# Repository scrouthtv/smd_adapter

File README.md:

# Generic Adapters for SMD to THT
All SMD adapters are for 2.54mm header

## SOIC-16 -- small version

## SOIC-18 -- wide version

## SC-70-6

## SON10
Mostly used by european companies as the step is 1mm (I guess).

# Plugs
## MQ172 3-pin

No warranty for anything in this repo.

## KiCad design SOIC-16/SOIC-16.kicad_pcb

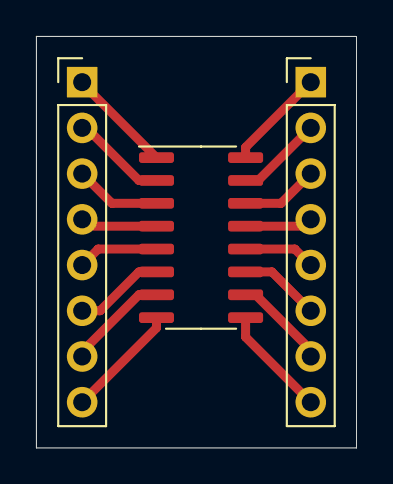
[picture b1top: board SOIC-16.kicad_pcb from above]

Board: 2 copper layers, 17.8 x 22.9 mm, 3 parts (0 on the bottom side), 16 nets.

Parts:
J1, J2: Conn_01x08; PinHeader_1x08_P2.54mm_Vertical
U1: NCV1413B; SOIC-16_3.9x9.9mm_P1.27mm

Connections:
unnamed: J1.1, U1.1
unnamed: J1.2, U1.2
unnamed: J1.3, U1.3
unnamed: J1.4, U1.4
unnamed: J1.5, U1.5
unnamed: J1.6, U1.6
unnamed: J1.7, U1.7
unnamed: J1.8, U1.8
unnamed: J2.1, U1.16
unnamed: J2.2, U1.15
unnamed: J2.3, U1.14
unnamed: J2.4, U1.13
unnamed: J2.5, U1.12
unnamed: J2.6, U1.11
unnamed: J2.7, U1.10
unnamed: J2.8, U1.9

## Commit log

2021-09-05 the pcbs
2021-09-05 gerbers
2021-09-05 added SO-18-wide
2021-09-05 added edge cuts
2021-09-05 added images
2021-09-06 SON10
2021-09-06 changed headers to 2.54
